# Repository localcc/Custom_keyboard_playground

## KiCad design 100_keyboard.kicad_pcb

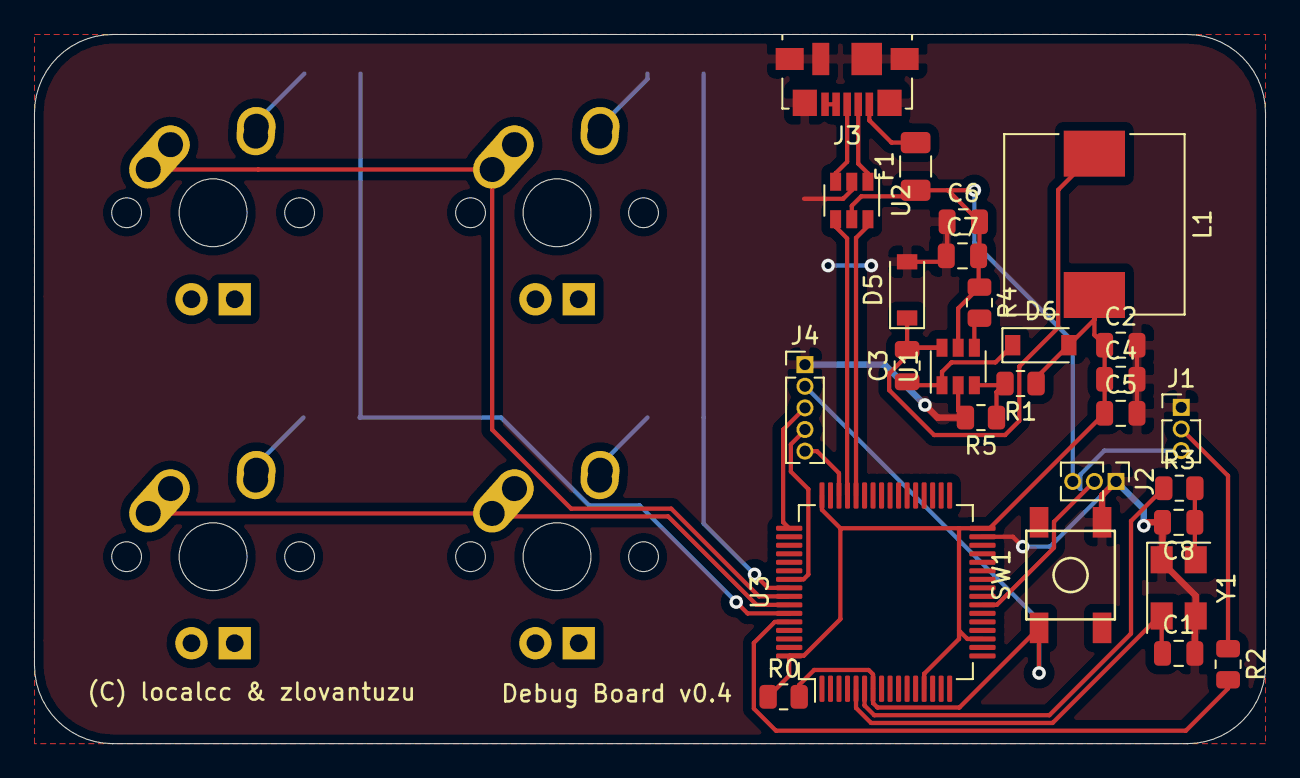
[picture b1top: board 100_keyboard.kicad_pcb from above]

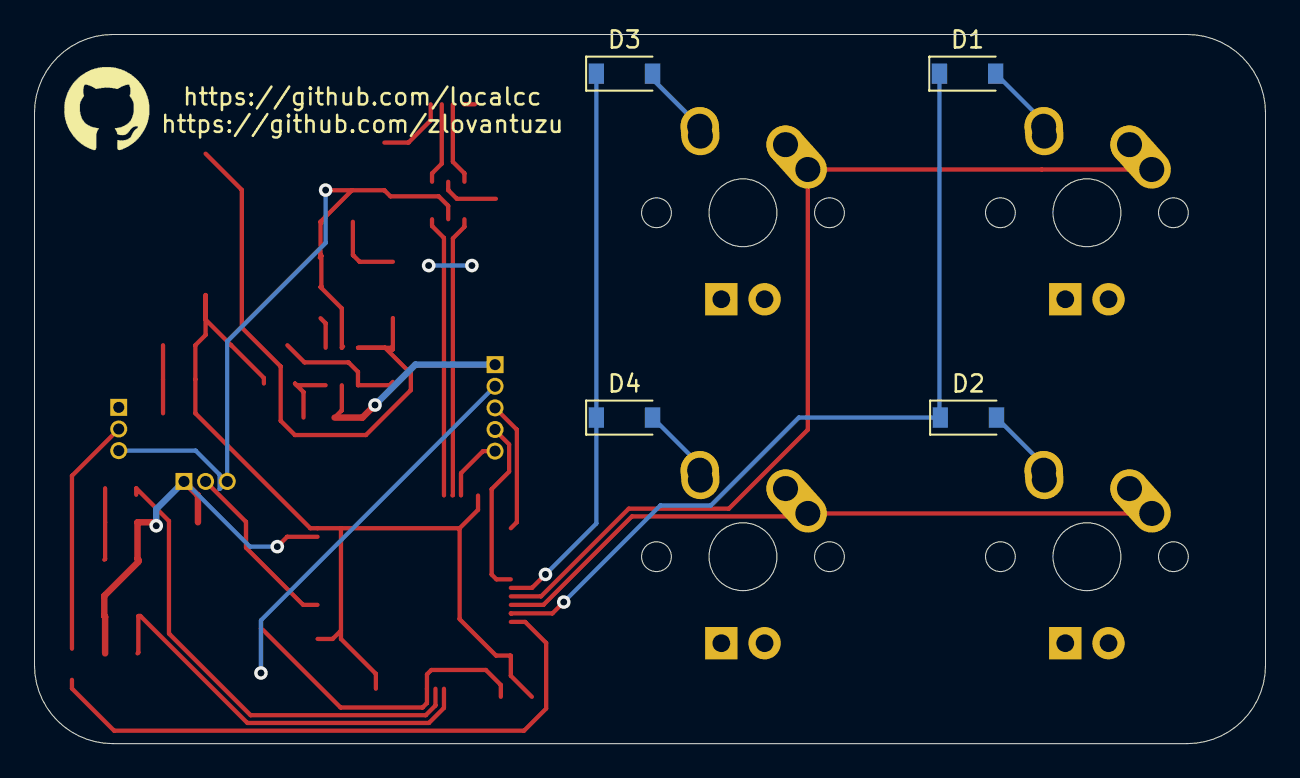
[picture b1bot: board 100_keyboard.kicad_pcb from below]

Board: 2 copper layers, 72.3 x 41.7 mm, 35 parts (4 on the bottom side), 30 nets.

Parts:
C1, C8: 12pF; C_0805_2012Metric
C2: 22uF 6.3V; C_0805_2012Metric
C3: 22nF; C_0805_2012Metric
C4, C5, C6, C7: 0.1uF; C_0805_2012Metric
D1, D2, D3, D4: D_Small; D_SOD-123
D5: D_Schottky; D_SOD-123
D6: 1N4148; D_SOD-123
F1: 500mA; Fuse_1206_3216Metric
J1, J2: Conn_01x03; PinHeader_1x03_P1.27mm_Vertical
J3: USB_B_Micro; USB_Micro-B_Molex_47346-0001
J4: Conn_01x05; PinHeader_1x05_P1.27mm_Vertical
L1: 47uH/1.66A; L_10.4x10.4_H4.8
MX1, MX2, MX3, MX4: MX-NoLED; MX-1U
R0: 10k; R_0805_2012Metric
R1: 50kOhm; R_0805_2012Metric
R2: 10K; R_0805_2012Metric
R3: 47; R_0805_2012Metric
R4: 100kOhm; R_0805_2012Metric
R5: 16.2kOhm; R_0805_2012Metric
SW1: SW_Push; SKQG-1155865
U1: mp2359; SOT-23-6
U2: USBLC6-2SC6; SOT-23-6
U3: STM32F103RBTx; LQFP-64_10x10mm_P0.5mm
Y1: 16MHz; Crystal_SMD_5032-4Pin_5.0x3.2mm

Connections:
3.3V: C2.1, C4.1, C5.1, D6.2, L1.2, R0.1, R1.1, U3.13, U3.19, U3.32, U3.48, U3.64
+5V: C6.2, C7.2, F1.1, J1.3, J2.3, R4.1, U1.5, U2.5
BOOT0: R2.2, U3.60
COL0: MX1.1, MX3.1, U3.57
COL1: MX2.1, MX4.1, U3.58
GND: C1.2, C2.2, C4.2, C5.2, C6.1, C7.1, C8.2, D5.2, J1.1, J2.1, J3.5, J3.6, J4.1, R5.2, SW1.2, U1.2, U2.2, U3.12, U3.18, U3.31, U3.47, U3.63, Y1.1, Y1.3
HSE_IN: C1.1, U3.5, Y1.2
HSE_OUT: R3.1, U3.6
LED_SPI: J2.2, U3.23
NRST: J4.2, R0.2, SW1.1, U3.7
unnamed: C3.1, D6.1, U1.1
unnamed: C3.2, D5.1, L1.1, U1.6
unnamed: C8.1, R3.2, Y1.4
unnamed: D1.2, MX1.2
unnamed: D2.2, MX2.2
unnamed: D3.2, MX3.2
unnamed: D4.2, MX4.2
unnamed: J1.2, R2.1
unnamed: R1.2, R5.1, U1.3
unnamed: R4.2, U1.4
ROW0: D1.1, D2.1, U3.59
ROW1: D3.1, D4.1, U3.56
SWDCLK: J4.3, U3.49
SWDIO: J4.5, U3.46
SWO: J4.4, U3.55
USB_DM: U2.6, U3.44
USB_DM_CONN: J3.2, U2.1
USB_DP: U2.4, U3.45
USB_DP_CONN: J3.3, U2.3
VCC: F1.2, J3.1

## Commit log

2020-10-26 Submodule Add
2020-10-27 Debug Board Files Added
2020-10-27 Create LICENSE
2020-11-17 Keyboard updates
2020-12-20 Debug board v0.2
2021-02-02 Debug Board v0.3
2021-03-06 Rev 0.4 schematic
2021-03-08 Debug board v0.4 beginnings
2021-03-08 Actual merge conflict fix
2021-03-08 Debug board v0.4 is almost done
2021-03-08 Debug board v0.4 done
